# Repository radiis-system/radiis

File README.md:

# RadIIS - the Radioactive Isotope Identifying Spectrometer

RadIIS is an open-source and industrial grade gamma spectrometer with automatic isotope identification.

It can be used as a handheld device, connected to a mobile phone (or tablet, pc, …) or as a monitoring station with backup battery, wide-range power input and long-range data transfer (LoRa).

> [!NOTE]
> This repository is currently transferred from a private repository. As different licenses for numerous files must be respected, this takes some time. Please stay tuned

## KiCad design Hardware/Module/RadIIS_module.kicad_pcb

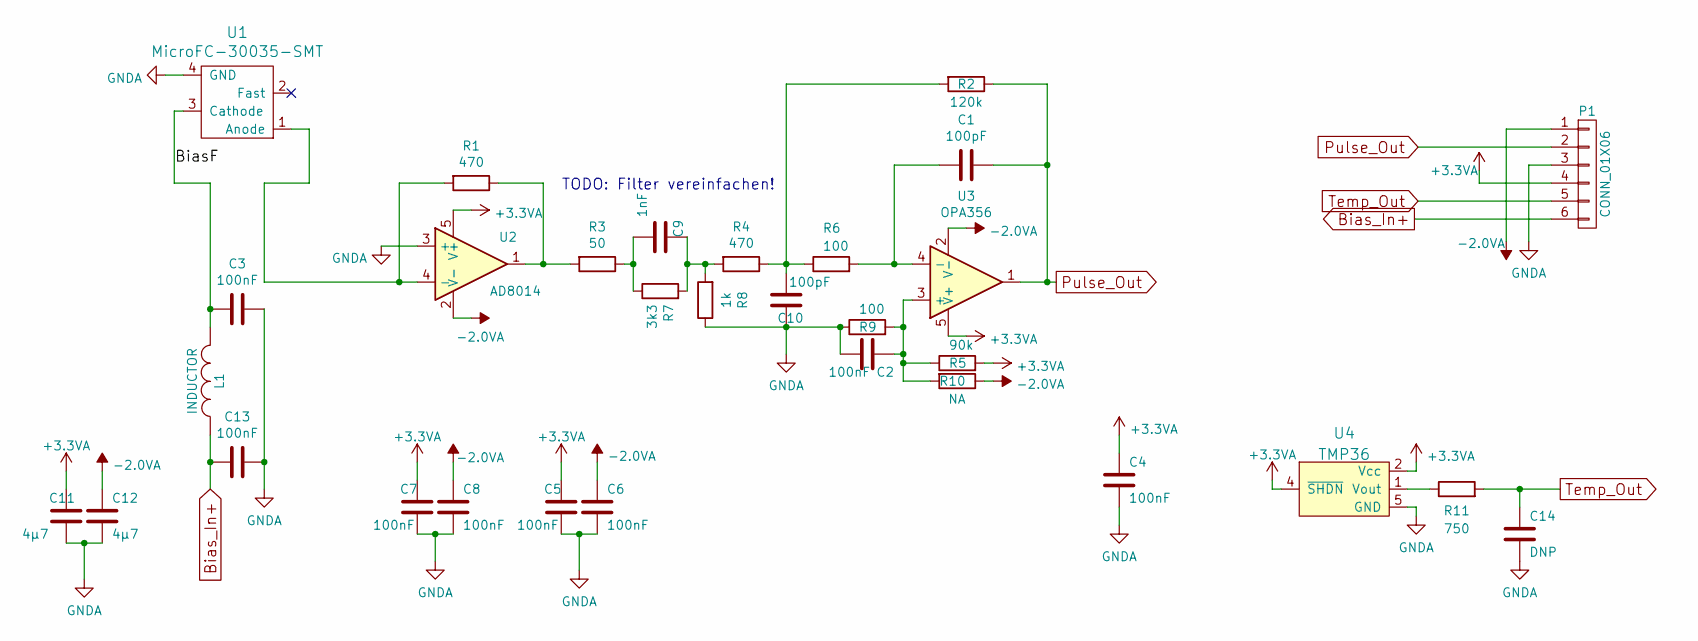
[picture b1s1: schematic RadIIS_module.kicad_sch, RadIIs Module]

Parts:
C1, C10: 100pF; C_0603_1608Metric; Digikey Nr 311-1069-1-ND
C2, C3, C4, C5, C6, C7, C8, C13: 100nF; C_0603_1608Metric; Digikey Nr 1292-1392-1-ND
C9: 1nF; C_0603_1608Metric; Digikey Nr 1292-1475-1-ND
C11, C12: 4µ7; C_1206_3216Metric; Digikey Nr 1276-3181-1-ND
C14: DNP; C_0603_1608Metric
L1: INDUCTOR; L_1206_3216Metric; Digikey Nr 240-2413-1-ND
P1: CONN_01X06; CardEdgeConnector; Digikey Nr NA
R1, R4: 470; R_0603_1608Metric; Digikey Nr 311-470HRCT-ND
R2: 120k; R_0603_1608Metric; Digikey Nr 311-120KHRCT-ND
R3: 50; R_0603_1608Metric; Digikey Nr 311-51.0HRCT-ND
R5: 90k; R_0603_1608Metric; Digikey Nr 311-90.9KHRCT-ND
R6, R9: 100; R_0603_1608Metric; Digikey Nr 311-100HRCT-ND
R7: 3k3; R_0603_1608Metric; Digikey Nr 311-3.30KHRCT-ND
R8: 1k; R_0603_1608Metric; Digikey Nr 311-1.00KHRCT-ND
R10: NA; R_0603_1608Metric; Digikey Nr NA
R11: 750; R_0603_1608Metric; Digikey Nr 311-100HRCT-ND
U1: MicroFC-30035-SMT; MicroFC-30035-SMT-C1; Digikey Nr MICROFC-30035-SMT-TR1OS-ND
U2: AD8014; SOT-23-5; Digikey Nr AD8014ARTZ-REEL7CT-ND
U3: OPA356; SOT-23-5; Digikey Nr 296-32191-1-ND
U4: TMP36; SOT-23-5; Digikey Nr TMP36GRTZ-REEL7CT-ND

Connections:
+3.3VA: C4.2, C5.2, C7.2, C11.2, P1.4, R5.2, U2.5 (V+), U3.5 (V+), U4.2 (Vcc), U4.4 (~SHDN)
-2.0VA: C6.2, C8.2, C12.2, P1.1, R10.1, U2.2 (V-), U3.2 (V-)
/BiasF: C3.2, L1.2, U1.3 (Cathode)
Bias_In+: C13.2, L1.1, P1.6
GNDA: C2.2, C3.1, C4.1, C5.1, C6.1, C7.1, C8.1, C10.2, C11.1, C12.1, C13.1, C14.1, P1.3, R8.1, R9.1, U1.4 (GND), U2.3 (+), U4.5 (GND)
unnamed: C1.2, R6.2, U3.4 (-)
unnamed: C2.1, R5.1, R9.2, R10.2, U3.3 (+)
unnamed: C9.1, R3.1, R7.1
unnamed: C9.2, R4.2, R7.2, R8.2
unnamed: C10.1, R2.2, R4.1, R6.1
unnamed: R1.1, R3.2, U2.1
unnamed: R1.2, U1.1 (Anode), U2.4 (-)
unnamed: R11.1, U4.1 (Vout)
Pulse_Out: C1.1, P1.2, R2.1, U3.1
Temp_Out: C14.2, P1.5, R11.2

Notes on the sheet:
TODO: Filter vereinfachen!

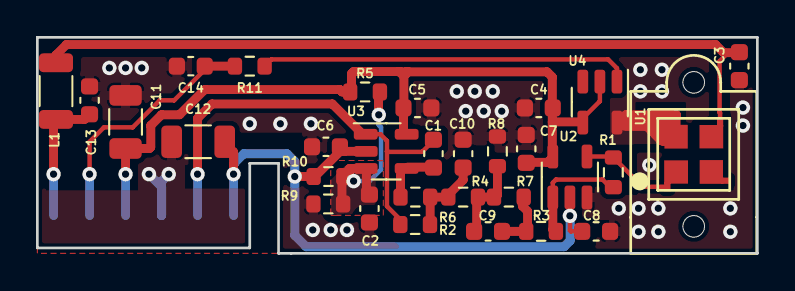
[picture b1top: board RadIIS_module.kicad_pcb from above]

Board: 2 copper layers, 40.0 x 12.0 mm, 31 parts (1 on the bottom side), 15 nets.

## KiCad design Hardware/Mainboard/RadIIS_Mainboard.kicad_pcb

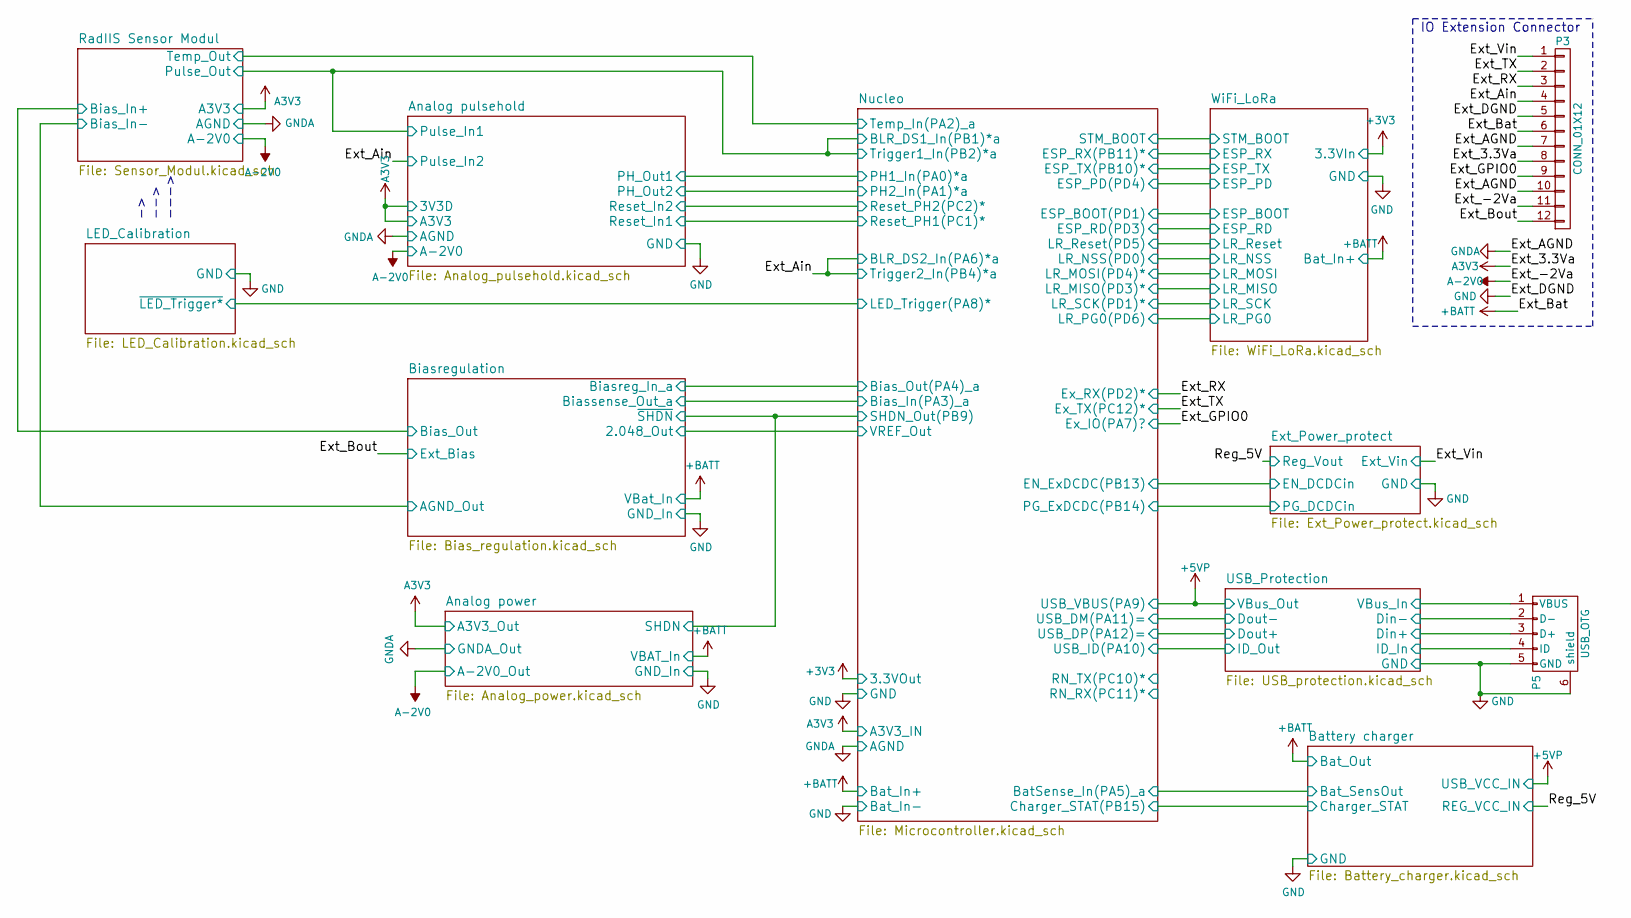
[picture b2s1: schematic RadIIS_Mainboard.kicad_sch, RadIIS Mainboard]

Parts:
P3: CONN_01X12; Hirose_FH12-12S-0.5SH_1x12-1MP_P0.50mm_Horizontal; Digikey Nr HFJ112CT-ND
P5: USB_OTG; MUSBK152XX; Digikey Nr MUSBK15230-ND

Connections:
+BATT: P3.6; also elsewhere on the board
/Ext_Ain: P3.4; also elsewhere on the board
/Ext_Bout: P3.12; also elsewhere on the board
/Ext_GPIO0: P3.9; also elsewhere on the board
/Ext_RX: P3.3; also elsewhere on the board
/Ext_TX: P3.2; also elsewhere on the board
/Ext_Vin: P3.1; also elsewhere on the board
/USB_Protection/Din+: P5.3 (D+); also elsewhere on the board
/USB_Protection/Din-: P5.2 (D-); also elsewhere on the board
/USB_Protection/ID_In: P5.4 (ID); also elsewhere on the board
/USB_Protection/VBus_In: P5.1 (VBUS); also elsewhere on the board
A3V3: P3.8; also elsewhere on the board
A-2V0: P3.11; also elsewhere on the board
GND: P3.5, P3.7, P3.10, P5.5 (GND), P5.6 (shield); also elsewhere on the board

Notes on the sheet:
IO Extension Connector
-> --> --->

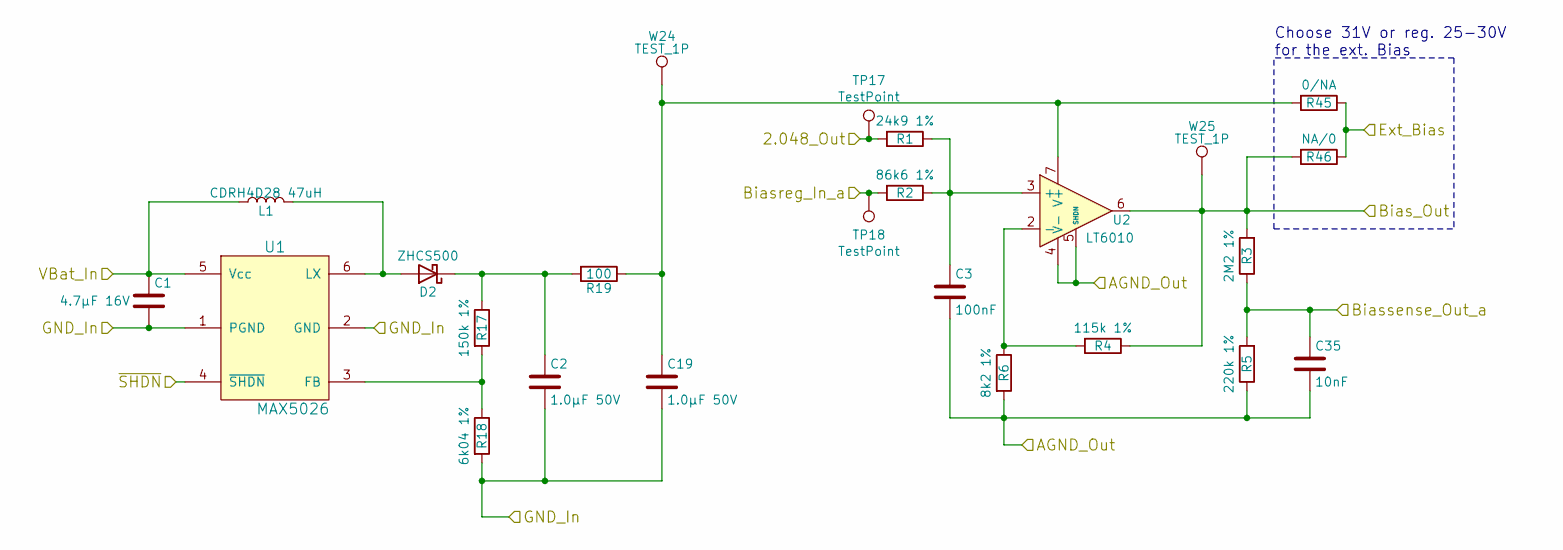
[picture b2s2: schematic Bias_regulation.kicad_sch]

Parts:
C1: 4.7µF 16V; C_0805_2012Metric; Digikey Nr 1276-1065-1-ND
C2, C19: 1.0µF 50V; C_0805_2012Metric; Digikey Nr 1276-6470-1-ND
C3: 100nF; C_0603_1608Metric; Digikey Nr 1276-1000-1-ND
C35: 10nF; C_0603_1608Metric; Digikey Nr 1276-1009-1-ND
D2: ZHCS500; D_SOT-23_ANK; Digikey Nr ZHCS500CT-ND
L1: CDRH4D28 47uH; CDRH4d28_FP; Digikey Nr 308-2182-1-ND
R1: 24k9 1%; R_0603_1608Metric; Digikey Nr 311-24.9KHRCT-ND
R2: 86k6 1%; R_0603_1608Metric; Digikey Nr 311-86.6KHRCT-ND
R3: 2M2 1%; R_0603_1608Metric; Digikey Nr YAG3329CT-ND
R4: 115k 1%; R_0603_1608Metric; Digikey Nr 311-115KHRCT-ND
R5: 220k 1%; R_0603_1608Metric; Digikey Nr 311-220KHRCT-ND
R6: 8k2 1%; R_0603_1608Metric; Digikey Nr 311-8.20KHRCT-ND
R17: 150k 1%; R_0603_1608Metric; Digikey Nr 311-150KHRCT-ND
R18: 6k04 1%; R_0603_1608Metric; Digikey Nr 311-150KHRCT-ND
R19: 100; R_0603_1608Metric; Digikey Nr 311-100HRCT-ND
R45: 0/NA; R_0603_1608Metric; Digikey Nr 311-0.0GRCT-ND
R46: NA/0; R_0603_1608Metric; Digikey Nr 311-0.0GRCT-ND
TP17, TP18: TestPoint; TestPoint_Pad_D1.5mm
U1: MAX5026; SOT-23-6; Digikey Nr MAX5026EUT+TCT-ND
U2: LT6010; SOIC-8_3.9x4.9mm_P1.27mm; Digikey Nr LT6010CS8#PBF-ND
W24, W25: TEST_1P; Socket_Strip_Straight_1x01_Pitch1.27mm; Digikey Nr NA

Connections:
+BATT: C1.1, L1.1, U1.5 (Vcc); also elsewhere on the board
/Analog power/SHDN: U1.4 (~SHDN); also elsewhere on the board
/Biasregulation/2.048_Out: R1.2, TP17.1; also elsewhere on the board
/Ext_Bout: R45.1, R46.1; also elsewhere on the board
/Nucleo/Bias_In(PA3)_a: C35.1, R3.1, R5.2; also elsewhere on the board
/Nucleo/Bias_Out(PA4)_a: R2.2, TP18.1; also elsewhere on the board
/RadIIS Sensor Modul/Bias_In+: R3.2, R4.1, R46.2, U2.6, W25.1; also elsewhere on the board
GND: C1.2, C2.2, C3.2, C19.2, C35.2, R5.1, R6.2, R18.2, U1.1 (PGND), U1.2 (GND), U2.4 (V-), U2.5 (SHDN); also elsewhere on the board
unnamed: C2.1, D2.1 (K), R17.1, R19.2
unnamed: C3.1, R1.1, R2.1, U2.3 (+)
unnamed: C19.1, R19.1, R45.2, U2.7 (V+), W24.1
unnamed: D2.2 (A), L1.2, U1.6 (LX)
unnamed: R4.2, R6.1, U2.2 (-)
unnamed: R17.2, R18.1, U1.3 (FB)

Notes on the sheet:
Choose 31V or reg. 25-30V for the ext. Bias

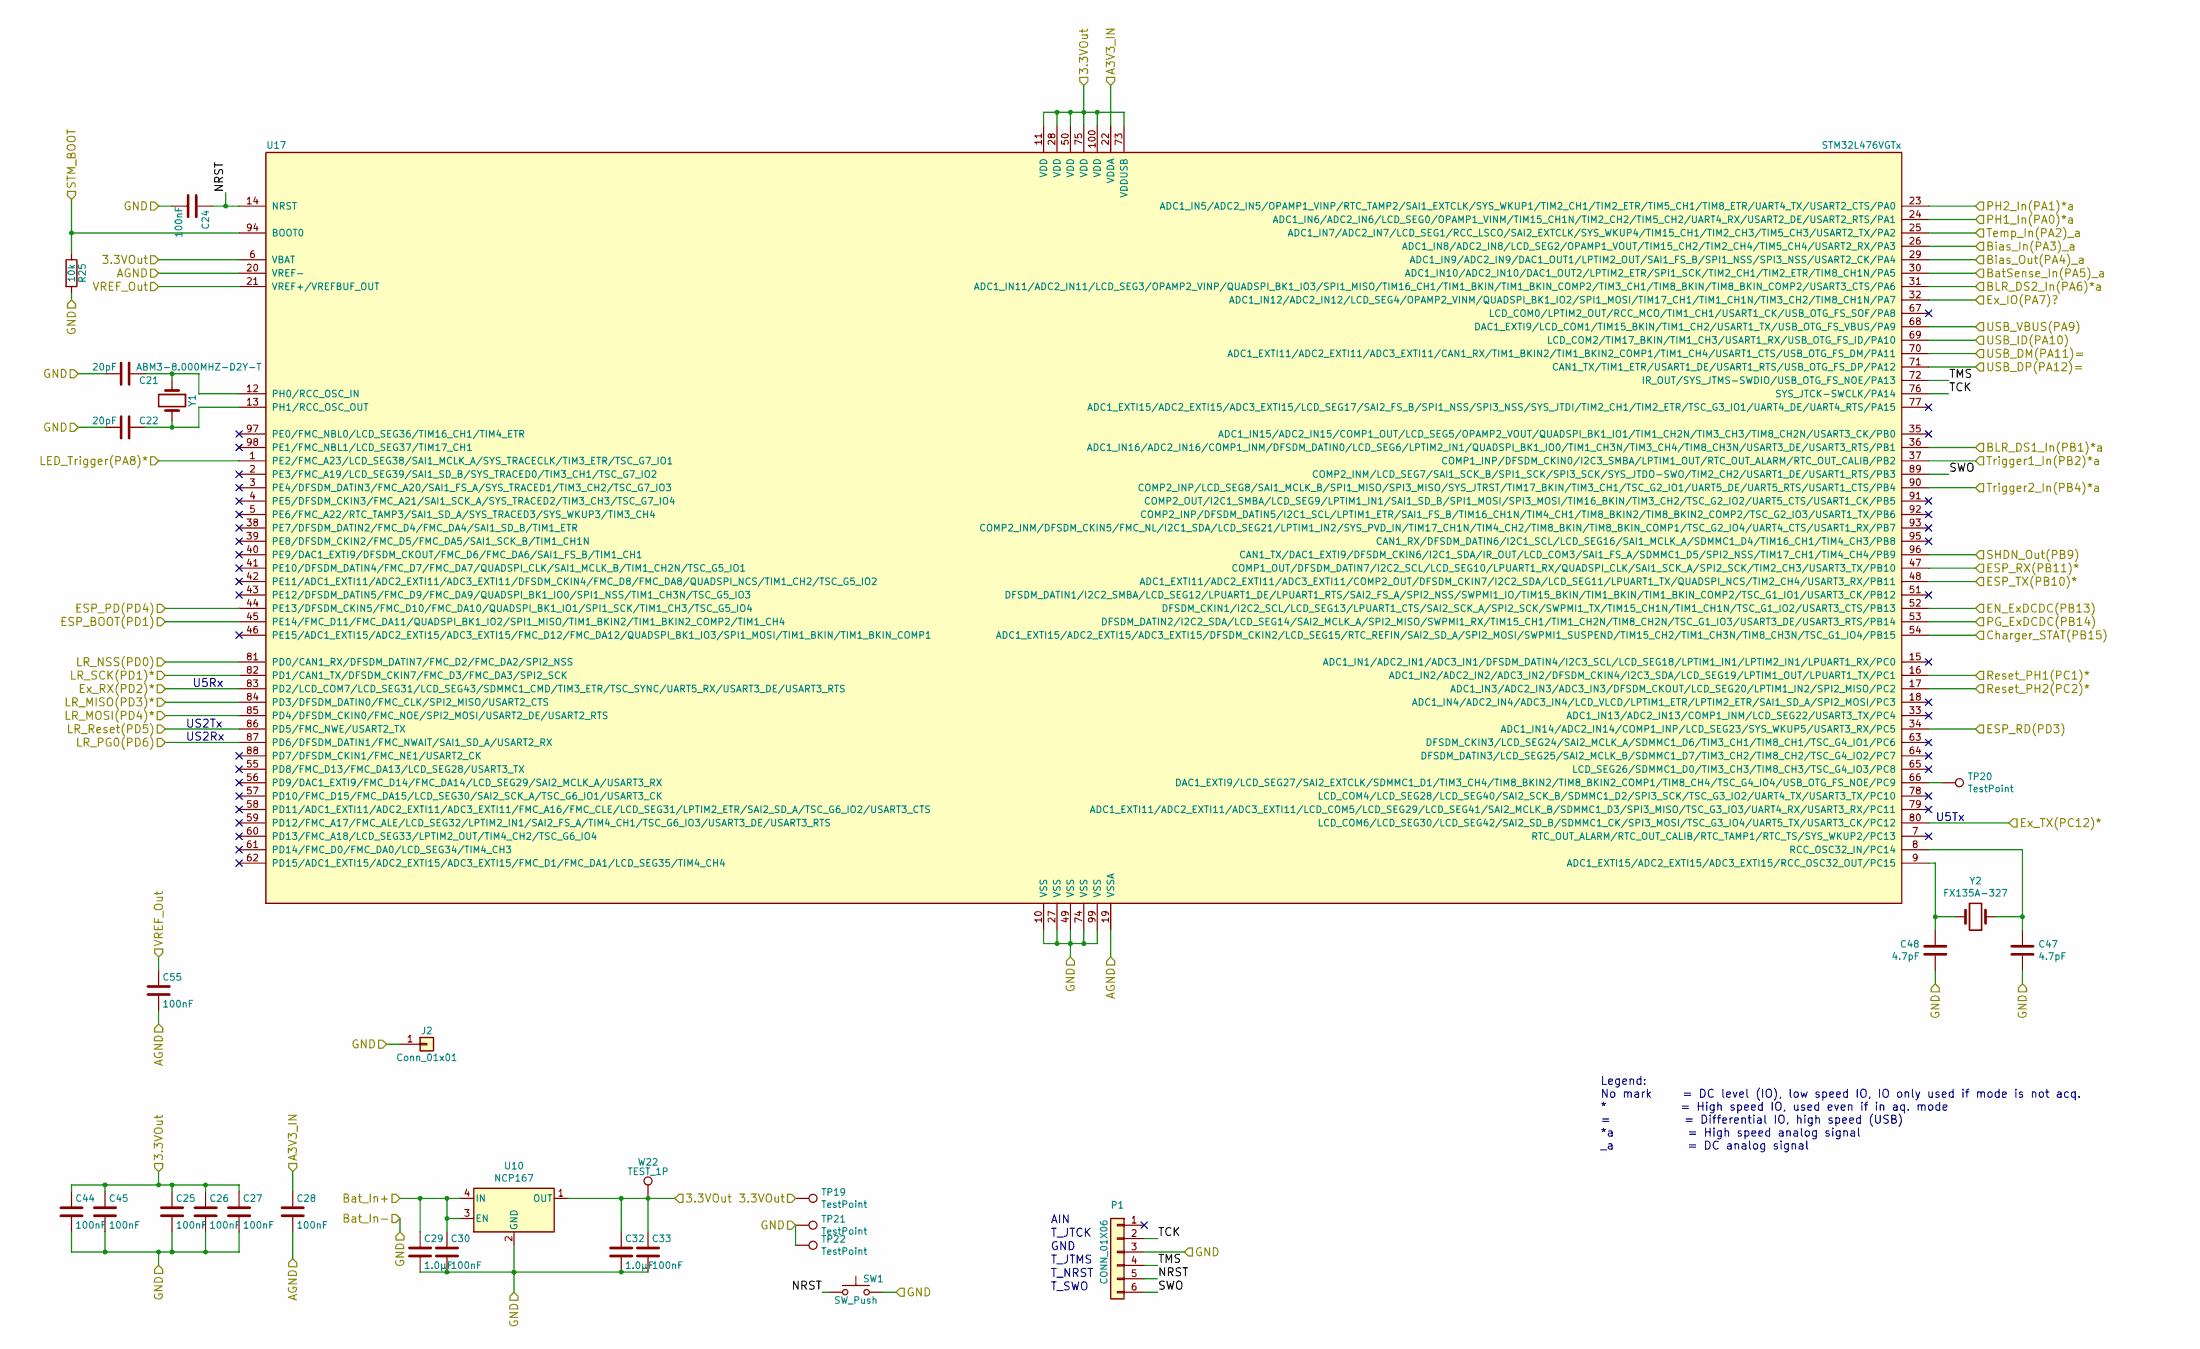
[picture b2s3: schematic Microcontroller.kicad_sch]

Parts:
C21, C22: 20pF; C_0603_1608Metric; Digikey Nr 1276-1187-1-ND
C24, C25, C26, C27, C28, C30, C33, C44, C45, C55: 100nF; C_0603_1608Metric; Digikey Nr 1276-1000-1-ND
C29, C32: 1.0µF; C_0805_2012Metric; Digikey Nr 1276-2931-1-ND
C47, C48: 4.7pF; C_0603_1608Metric; Digikey Nr 311-1740-1-ND
J2: Conn_01x01; PinHeader_1x01_P1.27mm_Vertical; Digikey Nr NA
P1: CONN_01X06; Pin_Header_Straight_1x06_Pitch1.27mm; Digikey Nr NA
R25: 10k; R_0603_1608Metric; Digikey Nr 311-10.0KHRCT-ND
SW1: SW_Push; SW_SPST_PTS810; Digikey Nr CKN10503CT-ND
TP19, TP20, TP21, TP22: TestPoint; TestPoint_Pad_D1.5mm
U10: NCP167; XDFN4
U17: STM32L476VGTx; LQFP-100_14x14mm_P0.5mm; Digikey Nr 497-15873-ND
W22: TEST_1P; Measurement_Point_Round-SMD-Pad_Small; Digikey Nr NA
Y1: ABM3-8.000MHZ-D2Y-T; Crystal_SMD_Abracon_ABM3-2Pin_5.0x3.2mm; Digikey Nr 535-10630-1-ND
Y2: FX135A-327; Crystal_SMD_G8-2Pin_3.2x1.5mm; Digikey Nr 631-1002-1-ND

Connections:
+3V3: C25.1, C26.1, C27.1, C32.1, C33.1, C44.1, C45.1, TP19.1, U10.1 (OUT), U17.6 (VBAT), U17.11 (VDD), U17.28 (VDD), U17.50 (VDD), U17.73 (VDDUSB), U17.75 (VDD), U17.100 (VDD), W22.1; also elsewhere on the board
+5VP: U17.68 (DAC1_EXTI9/LCD_COM1/TIM15_BKIN/TIM1_CH2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); also elsewhere on the board
+BATT: C29.1, C30.1, U10.3 (EN), U10.4 (IN); also elsewhere on the board
/Analog power/SHDN: U17.96 (CAN1_TX/DAC1_EXTI9/DFSDM_CKIN6/I2C1_SDA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); also elsewhere on the board
/Analog pulsehold/Reset_In1: U17.16 (ADC1_IN2/ADC2_IN2/ADC3_IN2/DFSDM_CKIN4/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); also elsewhere on the board
/Analog pulsehold/Reset_In2: U17.17 (ADC1_IN3/ADC2_IN3/ADC3_IN3/DFSDM_CKOUT/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); also elsewhere on the board
/Battery charger/Charger_STAT: U17.54 (ADC1_EXTI15/ADC2_EXTI15/ADC3_EXTI15/DFS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); also elsewhere on the board
/Biasregulation/2.048_Out: C55.1, U17.21 (VREF+/VREFBUF_OUT); also elsewhere on the board
/Ext_Ain: U17.31 (ADC1_IN11/ADC2_IN11/LCD_SEG3/OPAMP2_VIN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), U17.90 (COMP2_INP/LCD_SEG8/SAI1_MCLK_B/SPI1_MIS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); also elsewhere on the board
/Ext_GPIO0: U17.32 (ADC1_IN12/ADC2_IN12/LCD_SEG4/OPAMP2_VIN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); also elsewhere on the board
/Ext_Power_protect/EN_DCDCin: U17.52 (DFSDM_CKIN1/I2C2_SCL/LCD_SEG13/LPUART1_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); also elsewhere on the board
/Ext_Power_protect/PG_DCDCin: U17.53 (DFSDM_DATIN2/I2C2_SDA/LCD_SEG14/SAI2_MC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); also elsewhere on the board
/Ext_RX: U17.83 (PD2/LCD_COM7/LCD_SEG31/LCD_SEG43/SDMMC1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); also elsewhere on the board
/Ext_TX: U17.80 (LCD_COM6/LCD_SEG30/LCD_SEG42/SAI2_SD_B/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); also elsewhere on the board
/Nucleo/BLR_DS1_In(PB1)*a: U17.36 (ADC1_IN16/ADC2_IN16/COMP1_INM/DFSDM_DAT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), U17.37 (COMP1_INP/DFSDM_CKIN0/I2C3_SMBA/LPTIM1_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); also elsewhere on the board
/Nucleo/BatSense_In(PA5)_a: U17.30 (ADC1_IN10/ADC2_IN10/DAC1_OUT2/LPTIM2_ET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); also elsewhere on the board
/Nucleo/Bias_In(PA3)_a: U17.26 (ADC1_IN8/ADC2_IN8/LCD_SEG2/OPAMP1_VOUT/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); also elsewhere on the board
/Nucleo/Bias_Out(PA4)_a: U17.29 (ADC1_IN9/ADC2_IN9/DAC1_OUT1/LPTIM2_OUT/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); also elsewhere on the board
/Nucleo/LED_Trigger(PA8)*: U17.1 (PE2/FMC_A23/LCD_SEG38/SAI1_MCLK_A/SYS_T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); also elsewhere on the board
/Nucleo/NRST: C24.1, P1.5, SW1.1, U17.14 (NRST)
/Nucleo/PH1_In(PA0)*a: U17.24 (ADC1_IN6/ADC2_IN6/LCD_SEG0/OPAMP1_VINM/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); also elsewhere on the board
/Nucleo/PH2_In(PA1)*a: U17.23 (ADC1_IN5/ADC2_IN5/OPAMP1_VINP/RTC_TAMP2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); also elsewhere on the board
/Nucleo/STM_BOOT: R25.1, U17.94 (BOOT0); also elsewhere on the board
/Nucleo/SWO: P1.6, U17.89 (COMP2_INM/LCD_SEG7/SAI1_SCK_B/SPI1_SCK/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)
/Nucleo/TCK: P1.2, U17.76 (SYS_JTCK-SWCLK/PA14)
/Nucleo/TMS: P1.4, U17.72 (IR_OUT/SYS_JTMS-SWDIO/USB_OTG_FS_NOE/PA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)
/Nucleo/Temp_In(PA2)_a: U17.25 (ADC1_IN7/ADC2_IN7/LCD_SEG1/RCC_LSCO/SAI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); also elsewhere on the board
/USB_Protection/Dout+: U17.71 (CAN1_TX/TIM1_ETR/USART1_DE/USART1_RTS/U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); also elsewhere on the board
/USB_Protection/Dout-: U17.70 (ADC1_EXTI11/ADC2_EXTI11/ADC3_EXTI11/CAN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); also elsewhere on the board
/USB_Protection/ID_In: U17.69 (LCD_COM2/TIM17_BKIN/TIM1_CH3/USART1_RX/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); also elsewhere on the board
/WiFi_LoRa/ESP_BOOT: U17.45 (PE14/FMC_D11/FMC_DA11/QUADSPI_BK1_IO2/S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); also elsewhere on the board
/WiFi_LoRa/ESP_PD: U17.44 (PE13/DFSDM_CKIN5/FMC_D10/FMC_DA10/QUADS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); also elsewhere on the board
/WiFi_LoRa/ESP_RD: U17.34 (ADC1_IN14/ADC2_IN14/COMP1_INP/LCD_SEG23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); also elsewhere on the board
/WiFi_LoRa/ESP_RX: U17.47 (COMP1_OUT/DFSDM_DATIN7/I2C2_SCL/LCD_SEG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); also elsewhere on the board
/WiFi_LoRa/ESP_TX: U17.48 (ADC1_EXTI11/ADC2_EXTI11/ADC3_EXTI11/COM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); also elsewhere on the board
/WiFi_LoRa/LR_MISO: U17.84 (PD3/DFSDM_DATIN0/FMC_CLK/SPI2_MISO/USAR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); also elsewhere on the board
/WiFi_LoRa/LR_MOSI: U17.85 (PD4/DFSDM_CKIN0/FMC_NOE/SPI2_MOSI/USART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); also elsewhere on the board
/WiFi_LoRa/LR_NSS: U17.81 (PD0/CAN1_RX/DFSDM_DATIN7/FMC_D2/FMC_DA2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); also elsewhere on the board
/WiFi_LoRa/LR_PG0: U17.87 (PD6/DFSDM_DATIN1/FMC_NWAIT/SAI1_SD_A/US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); also elsewhere on the board
/WiFi_LoRa/LR_Reset: U17.86 (PD5/FMC_NWE/USART2_TX); also elsewhere on the board
/WiFi_LoRa/LR_SCK: U17.82 (PD1/CAN1_TX/DFSDM_CKIN7/FMC_D3/FMC_DA3/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); also elsewhere on the board
A3V3: C28.1, U17.22 (VDDA); also elsewhere on the board
GND: C21.2, C22.2, C24.2, C25.2, C26.2, C27.2, C28.2, C29.2, C30.2, C32.2, C33.2, C44.2, C45.2, C47.2, C48.2, C55.2, J2.1, P1.3, R25.2, SW1.2, TP21.1, TP22.1, U10.2 (GND), U10.EPAD (GND), U17.10 (VSS), U17.19 (VSSA), U17.20 (VREF-), U17.27 (VSS), U17.49 (VSS), U17.74 (VSS), U17.99 (VSS); also elsewhere on the board
unnamed: C21.1, U17.12 (PH0/RCC_OSC_IN), Y1.1
unnamed: C22.1, U17.13 (PH1/RCC_OSC_OUT), Y1.2
unnamed: C47.1, U17.8 (RCC_OSC32_IN/PC14), Y2.1
unnamed: C48.1, U17.9 (ADC1_EXTI15/ADC2_EXTI15/ADC3_EXTI15/RCC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), Y2.2
unnamed: TP20.1, U17.66 (DAC1_EXTI9/LCD_SEG27/SAI2_EXTCLK/SDMMC1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)

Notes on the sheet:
T_JTMS
U5Tx
AIN
Legend: No mark = DC level (IO), low speed IO, IO only used if mode is not acq. * = High speed IO, used even if in aq. mode = = Differential IO, high speed (USB) *a = High speed analog signal _a = DC analog signal
US2Tx US2Rx
U5Rx
GND
T_JTCK
T_NRST
T_SWO

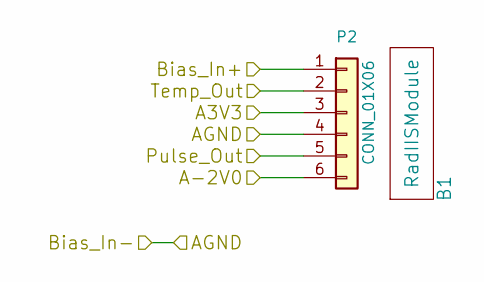
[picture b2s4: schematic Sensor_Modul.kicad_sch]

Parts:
B1: RadIISModule; Digikey Nr NA
P2: CONN_01X06; 6Pin_CardEdge_CON; Digikey Nr 581-009159006551906

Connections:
/Nucleo/BLR_DS1_In(PB1)*a: P2.5; also elsewhere on the board
/Nucleo/Temp_In(PA2)_a: P2.2; also elsewhere on the board
/RadIIS Sensor Modul/Bias_In+: P2.1; also elsewhere on the board
A3V3: P2.3; also elsewhere on the board
A-2V0: P2.6; also elsewhere on the board
GND: P2.4; also elsewhere on the board

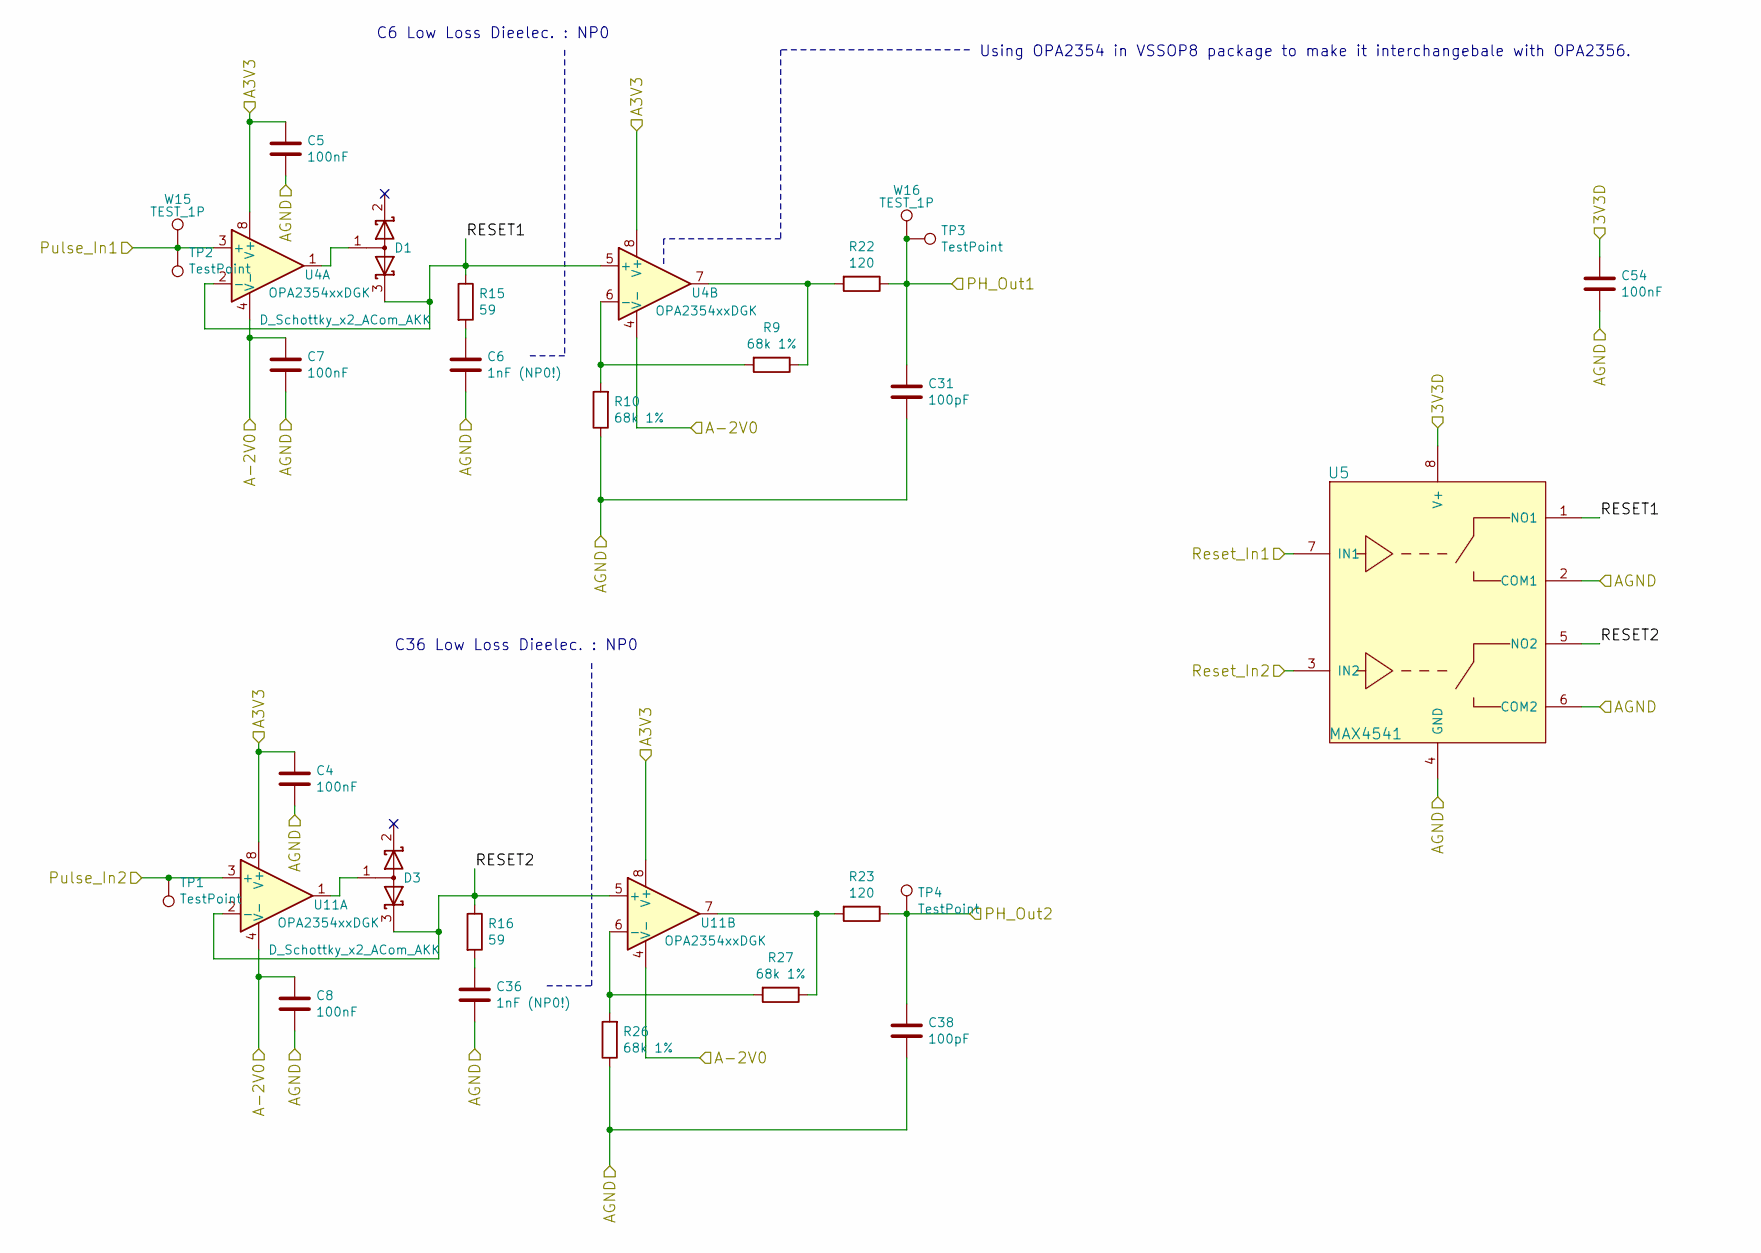
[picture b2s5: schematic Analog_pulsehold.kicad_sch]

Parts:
C4, C5, C7, C8, C54: 100nF; C_0603_1608Metric; Digikey Nr 1276-1000-1-ND
C6, C36: 1nF (NP0!); C_0603_1608Metric; Digikey Nr 1292-1475-1-ND
C31, C38: 100pF; C_0603_1608Metric; Digikey Nr 311-1069-1-ND
D1, D3: D_Schottky_x2_ACom_AKK; SOT-23; Digikey Nr MMBD301LT1GOSCT-ND
R9, R10, R26, R27: 68k 1%; R_0603_1608Metric; Digikey Nr 311-68.0KHRCT-ND
R15, R16: 59; R_0603_1608Metric; Digikey Nr 311-59.0HRCT-ND
R22, R23: 120; R_0603_1608Metric; Digikey Nr 311-120HRCT-ND
TP1, TP2, TP3, TP4: TestPoint; TestPoint_Pad_D1.5mm
U4, U11: OPA2354xxDGK; VSSOP-8_3.0x3.0mm_P0.65mm; Digikey Nr 296-12642-1-ND
U5: MAX4541; uMAX8; Digikey Nr MAX4541EUA+-ND
W15, W16: TEST_1P; Measurement_Point_Round-SMD-Pad_Small; Digikey Nr NA

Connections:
/Analog pulsehold/RESET1: D1.3 (K), R15.1, U4.2 (-), U4.5 (+), U5.1 (NO1)
/Analog pulsehold/RESET2: D3.3 (K), R16.1, U5.5 (NO2), U11.2 (-), U11.5 (+)
/Analog pulsehold/Reset_In1: U5.7 (IN1); also elsewhere on the board
/Analog pulsehold/Reset_In2: U5.3 (IN2); also elsewhere on the board
/Ext_Ain: TP1.1, U11.3 (+); also elsewhere on the board
/Nucleo/BLR_DS1_In(PB1)*a: TP2.1, U4.3 (+), W15.1; also elsewhere on the board
/Nucleo/PH1_In(PA0)*a: C31.1, R22.1, TP3.1, W16.1; also elsewhere on the board
/Nucleo/PH2_In(PA1)*a: C38.1, R23.1, TP4.1; also elsewhere on the board
A3V3: C4.1, C5.1, C54.1, U4.8 (V+), U5.8 (V+), U11.8 (V+); also elsewhere on the board
A-2V0: C7.2, C8.1, U4.4 (V-), U11.4 (V-); also elsewhere on the board
GND: C4.2, C5.2, C6.2, C7.1, C8.2, C31.2, C36.2, C38.2, C54.2, R10.1, R26.1, U5.2 (COM1), U5.4 (GND), U5.6 (COM2); also elsewhere on the board
unnamed: C6.1, R15.2
unnamed: C36.1, R16.2
unnamed: D1.1 (A), U4.1
unnamed: D3.1 (A), U11.1
unnamed: R9.2, R10.2, U4.6 (-)
unnamed: R9.1, R22.2, U4.7
unnamed: R23.2, R27.1, U11.7
unnamed: R26.2, R27.2, U11.6 (-)

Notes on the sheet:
C36 Low Loss Dieelec. : NP0
C6 Low Loss Dieelec. : NP0
Using OPA2354 in VSSOP8 package to make it interchangebale with OPA2356.

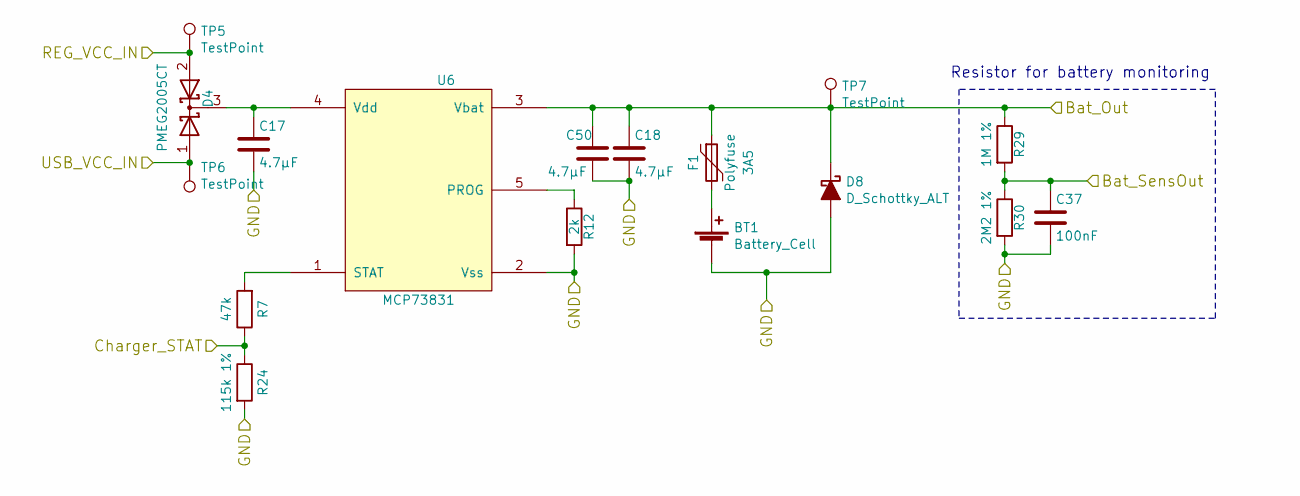
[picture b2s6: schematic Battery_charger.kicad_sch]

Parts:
BT1: Battery_Cell; PinHeader_1x02_P2.54mm_Vertical; Digikey Nr NA
C17, C18, C50: 4.7µF; C_0805_2012Metric; Digikey Nr 1276-1065-1-ND
C37: 100nF; C_0603_1608Metric; Digikey Nr 1276-1000-1-ND
D4: PMEG2005CT; SOT-23; Digikey Nr 1727-5188-1-ND
D8: D_Schottky_ALT; D_SOD-123F; Digikey Nr MBR230LSFT1GOSCT-ND
F1: Polyfuse; Fuse_1206_3216Metric; Digikey Nr MF-NSML175-2CT-ND
R7: 47k; R_0603_1608Metric; Digikey Nr 311-47.0KHRCT-ND
R12: 2k; R_0603_1608Metric; Digikey Nr 311-2.00KHRCT-ND
R24: 115k 1%; R_0603_1608Metric; Digikey Nr 311-115KHRCT-ND
R29: 1M 1%; R_0603_1608Metric; Digikey Nr 311-1.00MHRCT-ND
R30: 2M2 1%; R_0603_1608Metric; Digikey Nr YAG3329CT-ND
TP5, TP6, TP7: TestPoint; TestPoint_Pad_D1.5mm
U6: MCP73831; SOT-23-5; Digikey Nr MCP73831T-2ACI/OTCT-ND

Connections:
+5VP: D4.1 (A), TP6.1; also elsewhere on the board
+BATT: C18.1, C50.1, D8.1 (K), F1.1, R29.1, TP7.1, U6.3 (Vbat); also elsewhere on the board
/Battery charger/Charger_STAT: R7.1, R24.1; also elsewhere on the board
/Nucleo/BatSense_In(PA5)_a: C37.1, R29.2, R30.1; also elsewhere on the board
/Reg_5V: D4.2 (A), TP5.1; also elsewhere on the board
GND: BT1.2 (-), C17.2, C18.2, C37.2, C50.2, D8.2 (A), R12.2, R24.2, R30.2, U6.2 (Vss); also elsewhere on the board
unnamed: BT1.1 (+), F1.2
unnamed: C17.1, D4.3 (K), U6.4 (Vdd)
unnamed: R7.2, U6.1 (STAT)
unnamed: R12.1, U6.5 (PROG)

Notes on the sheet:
Resistor for battery monitoring

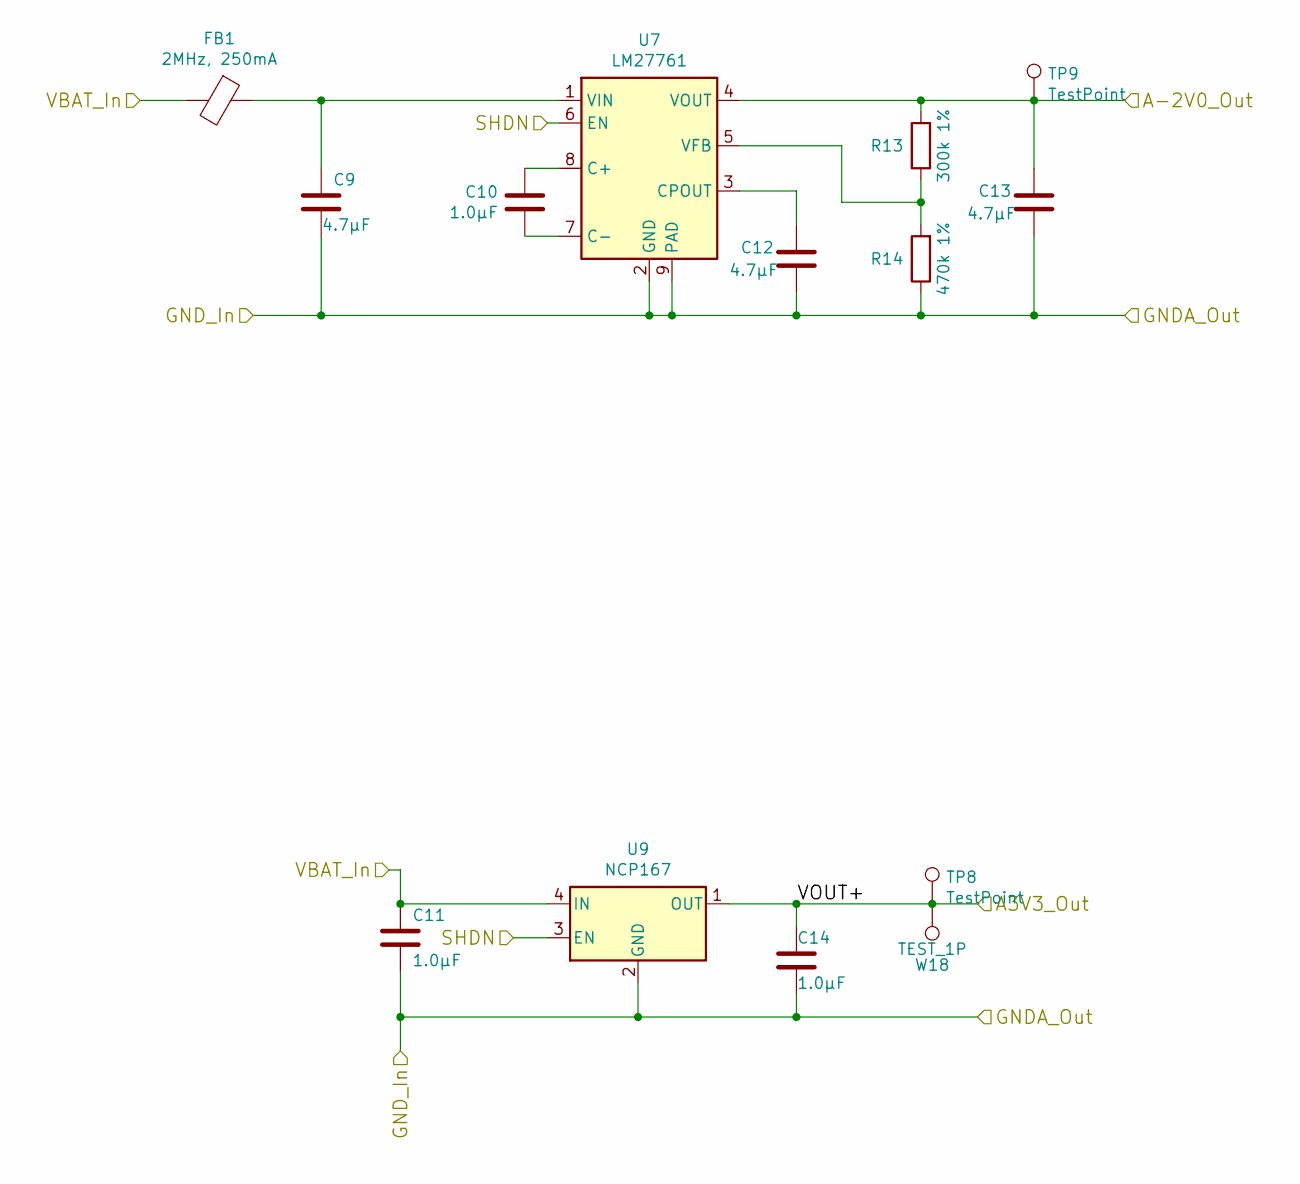
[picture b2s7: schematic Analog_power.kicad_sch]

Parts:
C9, C12, C13: 4.7µF; C_0805_2012Metric; Digikey Nr 1276-1065-1-ND
C10, C11, C14: 1.0µF; C_0805_2012Metric; Digikey Nr 1276-2931-1-ND
FB1: 2MHz, 250mA; L_0603_1608Metric; Digikey Nr 445-8694-1-ND
R13: 300k 1%; R_0603_1608Metric; Digikey Nr 311-300KHRCT-ND
R14: 470k 1%; R_0603_1608Metric; Digikey Nr 311-470KHRCT-ND
TP8, TP9: TestPoint; TestPoint_Pad_D1.5mm
U7: LM27761; WSON-8-1EP_2x2mm_P0.5mm_EP0.9x1.6mm; Digikey Nr 296-44379-1-ND
U9: NCP167; XDFN4
W18: TEST_1P; Measurement_Point_Round-SMD-Pad_Small; Digikey Nr NA

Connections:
+BATT: C11.1, FB1.2, U9.4 (IN); also elsewhere on the board
/Analog power/SHDN: U7.6 (EN), U9.3 (EN); also elsewhere on the board
A3V3: C14.1, TP8.1, U9.1 (OUT), W18.1; also elsewhere on the board
A-2V0: C13.1, R13.2, TP9.1, U7.4 (VOUT); also elsewhere on the board
GND: C9.2, C11.2, C12.2, C13.2, C14.2, R14.1, U7.2 (GND), U7.9 (PAD), U9.2 (GND), U9.EPAD (GND); also elsewhere on the board
unnamed: C9.1, FB1.1, U7.1 (VIN)
unnamed: C10.1, U7.8 (C+)
unnamed: C10.2, U7.7 (C-)
unnamed: C12.1, U7.3 (CPOUT)
unnamed: R13.1, R14.2, U7.5 (VFB)
